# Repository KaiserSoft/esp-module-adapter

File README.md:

The PCB design is using the ESP-12F footprint to align the pogo pins to the pads.
You should propably delete the ESP-12F footprint before exporting the gerber files.

Designed for  P75-E2 pogo pins

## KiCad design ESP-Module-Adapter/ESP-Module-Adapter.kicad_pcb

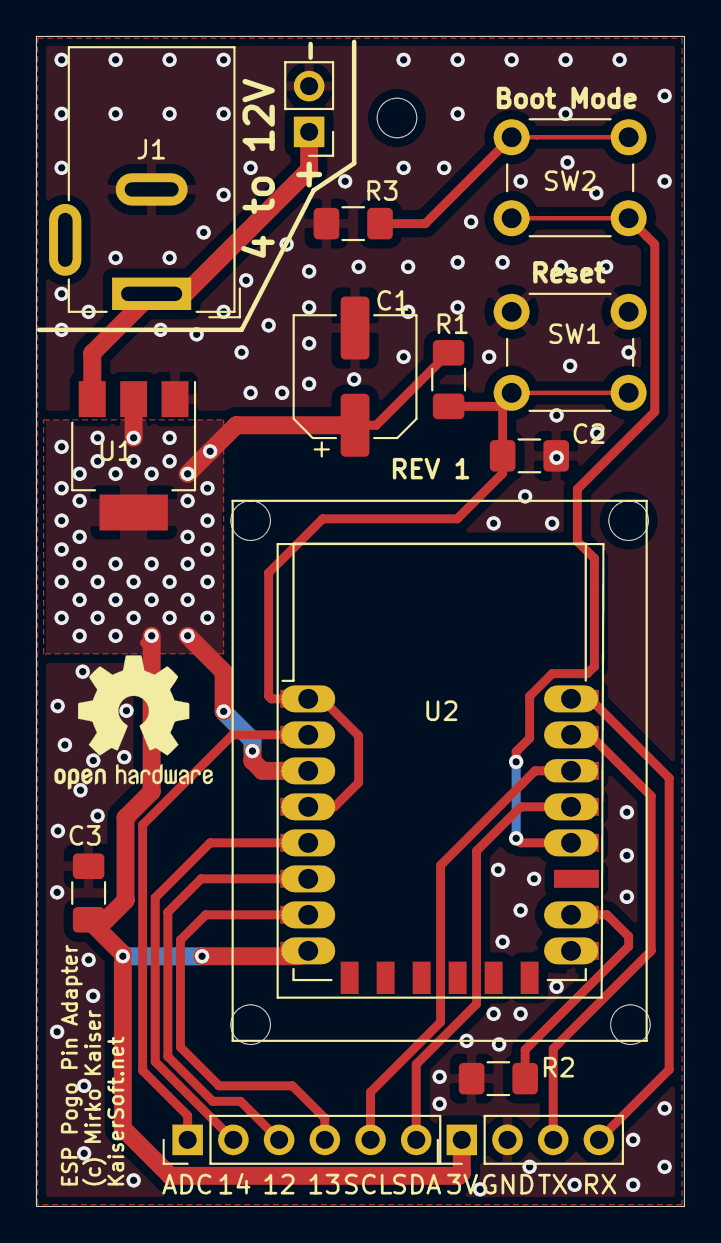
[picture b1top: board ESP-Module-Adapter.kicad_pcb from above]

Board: 2 copper layers, 36.0 x 65.0 mm, 14 parts (0 on the bottom side), 15 nets.

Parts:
C1: 47uF; CP_Elec_6.3x5.7
C2, C3: 100nF; C_1206_3216Metric_Pad1.42x1.75mm_HandSolder
J1: Barrel_Jack_Switch; BarrelJack_Wuerth_6941xx301002
J2: Conn_01x02; PinHeader_1x02_P2.54mm_Vertical
J3: Prog; PinHeader_1x04_P2.54mm_Vertical
J4: ESP Pins; PinHeader_1x06_P2.54mm_Vertical
R1, R2, R3: 10K; R_1206_3216Metric_Pad1.42x1.75mm_HandSolder
SW1: Reset; SW_PUSH_6mm
SW2: Boot Mode; SW_PUSH_6mm
U1: LD1117S33TR_SOT223; SOT-223-3_TabPin2
U2: ESP-12F; ESP-12E

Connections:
+3V3: C1.1, C3.1, J3.1, R1.1, U1.2, U2.3, U2.8
ADC: J4.1, U2.2
GND: C1.2, C2.2, C3.2, J1.2, J2.2, J3.2, R2.2, R3.2, SW1.1, U1.1, U2.15
GPIO4-SDA: J4.6, U2.19
GPIO5-SCL: J4.5, U2.20
GPIO12: J4.3, U2.6
GPIO13: J4.4, U2.7
GPIO14: J4.2, U2.5
unnamed: R2.1, U2.16
unnamed: R3.1, SW2.2
unnamed: SW2.1, U2.18
RST: C2.1, R1.2, SW1.2, U2.1, U2.4
RX: J3.4, U2.22
TX: J3.3, U2.21
VDC: J1.1, J2.1, U1.3

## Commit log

2019-08-30 * ordered this PCB from elecrow
